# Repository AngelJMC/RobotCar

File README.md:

# RobotCar

It is a personal project to convert an old radio control car into a prototype autonomous vehicle. 
More information in the project [Wiki page](https://github.com/AngelJMC/RobotCar/wiki).

## Getting Started

- [AMP 2.6 board](https://github.com/ArduPilot/ardupilot_wiki/blob/master/common/source/docs/common-apm25-and-26-overview.rst). You can use Arduino Mega 2560.
- [L298 Driver](http://candy-ho.com/Drivers/Guia%20de%20Uso%20L298.pdf), It is a dual H-bridge to control de DC motor.
- [LM2596 regulator](https://http2.mlstatic.com/modulo-step-down-dc-dc-mini-regulador-de-voltaje-lm2596-D_NQ_NP_828400-MLC26118955337_102017-F.jpg) Step-down DC-DC converter module, ~12v LiPo battery to 5v.

Atom with [PlatformIO](https://platformio.org/) plugin. If you prefer, you can use Arduino IDE.

### Prerequisites

You need install the next arduino library:
- [Encoder@>=1.4.1](https://github.com/PaulStoffregen/Encoder)
- [L298N@>=1.1.0](https://github.com/AndreaLombardo/L298N)
- [PID@>=1.2.](https://github.com/br3ttb/Arduino-PID-Library)
  
All other required libraries are included in the repository.

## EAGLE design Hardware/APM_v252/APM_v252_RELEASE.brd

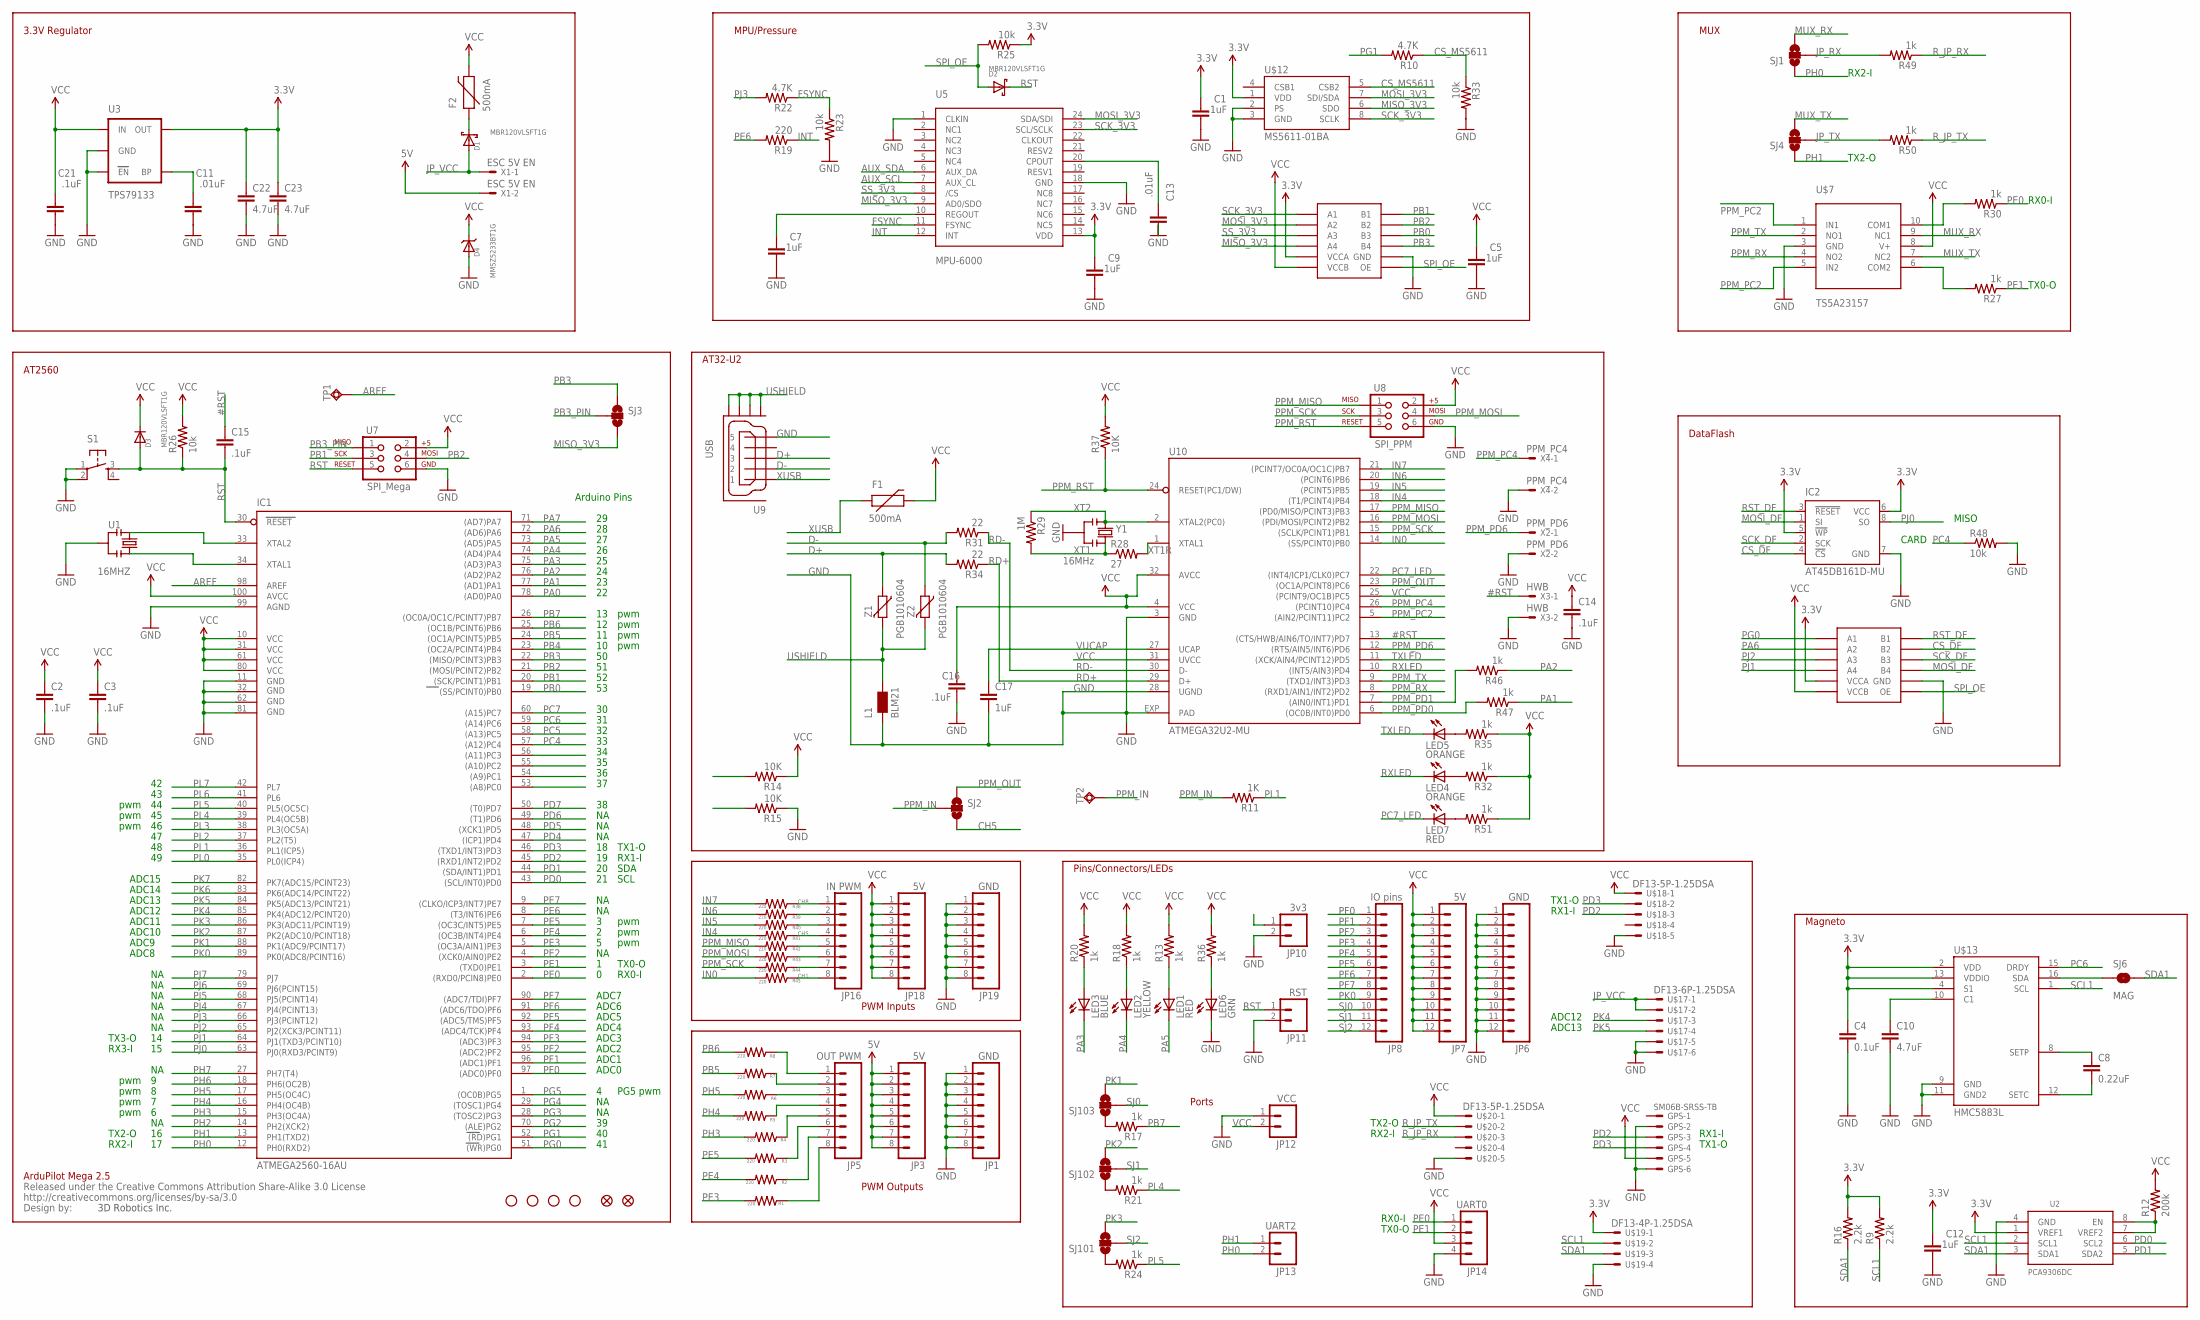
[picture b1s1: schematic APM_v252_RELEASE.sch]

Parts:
C1, C2, C3, C5, C7, C9, C12, C14, C15, C16, C21: .1uF; 0402-CAP
C4: 0.1uF; 0402-CAP
C8: 0.22uF; 0402-CAP
C10: 4.7uF; 1206
C11, C13: .01uF; 0402-CAP
C17: 1uF; 0402-CAP
C22, C23: 4.7uF; 0805
D1, D2, D3: MBR120VLSFT1G; SOD-123
D4: MMSZ5233BT1G; SOD-123
F1, F2: 500mA; PTC-1206
GPS: SM06B-SRSS-TB
IC1: ATMEGA2560-16AU; TQFP100
IC2: AT45DB161D-MU; VDFN-8-NO-BOTTOM-PAD
JP1, JP19: GND; 1X08
JP2, JP17: FIDUCIAL1X2; FIDUCIAL-1X2
JP3, JP18: 5V; 1X08
JP5: OUT PWM; 1X08
JP6: GND; 1X12
JP7: 5V; 1X12
JP8: IO pins; 1X12
JP10: 3v3; 1X02
JP11: RST; 1X02
JP12: VCC; 1X02
JP13: UART2; 1X02
JP14: UART0; 1X04
JP16: IN PWM; 1X08
L1: BLM21; 0805
LED1, LED7: RED; LED-0603
LED2: YELLOW; LED-0603
LED3: BLUE; LED-0603
LED4, LED5: ORANGE; LED-0603
LED6: GRN; LED-0603
R1, R2, R3, R4, R5, R6, R7, R8, R19, R38, R39, R40, R41, R42, R43, R44, R45: 220; 0402-RES
R9, R16: 2.2k; 0402-RES
R10, R22: 4.7K; 0402-RES
R11: 1K; 0402-RES
R12: 200k; 0402-RES
R13, R17, R18, R20, R21, R24, R27, R30, R32, R35, R36, R46, R47, R49, R50, R51: 1k; 0402-RES
R14, R15, R37: 10K; 0402-RES
R23, R25, R26, R33, R48: 10k; 0402-RES
R28: 27; 0402-RES
R29: 1M; 0402-RES
R31, R34: 22; 0402-RES
S1: TAC_SWITCHSMD; TACTILE_SWITCH_SMD
SJ1, SJ2, SJ3, SJ4: SOLDERJUMPER_2WAYT; SJ_2
SJ6: MAG; SJ_2S-TRACE
SJ101, SJ102, SJ103: SOLDERJUMPER_2WAYS; SJ_3
TP1, TP2: TPSQTP10SQ; TP10SQ
U1: 16MHZ; RESONATOR-SMD
U2: PCA9306DC; VSSOP8
U3: TPS79133; SOT23-5
U5: MPU-6000; QFN-24
U7: SPI_Mega; 2X3-NS
U8: SPI_PPM; 2X3-NS
U9: USB; MOLEX_MICRO_USB_AB_BOTTOM_MOUNT
U10: ATMEGA32U2-MU; QFN32
U$1, U$2, U$4, U$5: STAND-OFF
U$6: CREATIVE_COMMONS
U$7: TS5A23157; MSOP10
U$12: MS5611-01BA
U$13: HMC5883L; LPCC16
U$14, U$15: TXB0104UQFN; UQFN-12
U$17: DF13-6P-1.25DSA
U$18, U$20: DF13-5P-1.25DSA
U$19: DF13-4P-1.25DSA
X1: ESC 5V EN; 87758-0216
X2: PPM_PD6; 87758-0216
X3: HWB; 87758-0216
X4: PPM_PC4; 87758-0216
Y1: 16MHz; RESONATOR
Z1, Z2: PGB1010604; CT/CN0603

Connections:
3.3V: C1.2, C4.1, C9.2, C12.2, C22.1, C23.1, IC2.5 (!WP), IC2.6 (VCC), R9.2, R16.2, R25.1, U2.1 (VREF1), U3.5 (OUT), U5.13 (VDD), U$12.1 (VDD), U$13.2 (VDD), U$13.4 (S1), U$13.13 (VDDIO), U$14.1 (VCCA), U$15.1 (VCCA), U$19.1
5V: JP3.1, JP3.2, JP3.3, JP3.4, JP3.5, JP3.6, JP3.7, JP3.8, X1.2
#RST: C15.1, U10.13 ((CTS/HWB/AIN6/TO/INT7)PD7), X3.1
AREF: IC1.98 (AREF), TP1.TP
AUX_SCL: U5.7 (AUX_CL)
AUX_SDA: U5.6 (AUX_DA)
CH1: JP16.8, R45.1
CH5: JP16.4, R41.1, SJ2.3
CH8: JP16.1, R38.1
CS_DF: IC2.4 (!CS), U$15.9 (B2)
CS_MS5611: R10.1, R33.1, U$12.5 (CSB2)
D+: R34.2, U9.3, Z1.1
D-: R31.2, U9.2, Z2.1
FSYNC: R22.1, R23.1, U5.11 (FSYNC)
GND: C1.1, C2.2, C3.2, C4.2, C5.1, C7.1, C9.1, C10.2, C11.1, C12.1, C13.1, C14.2, C16.2, C17.2, C21.1, C22.2, C23.2, D4.A, GPS.2, GPS.6, IC1.11 (GND), IC1.32 (GND1), IC1.62 (GND2), IC1.81 (GND3), IC1.99 (AGND), IC2.7 (GND), JP1.1, JP1.2, JP1.3, JP1.4, JP1.5, JP1.6, JP1.7, JP1.8, JP6.1, JP6.2, JP6.3, JP6.4, JP6.5, JP6.6, JP6.7, JP6.8, JP6.9, JP6.10, JP6.11, JP6.12, JP10.2, JP11.2, JP12.1, JP14.4, JP19.1, JP19.2, JP19.3, JP19.4, JP19.5, JP19.6, JP19.7, JP19.8, L1.1, LED6.C, R15.1, R23.2, R33.2, R48.2, S1.1, S1.2, U1.2, U2.4 (GND), U3.2 (GND), U3.3 (EN), U5.1 (CLKIN), U5.18 (GND), U7.6, U8.6, U9.5, U10.3 (GND), U10.28 (UGND), U10.EXP (PAD), U$7.3 (GND), U$12.2 (PS), U$12.3 (GND), U$13.9 (GND), U$13.11 (GND2), U$14.6 (GND), U$15.6 (GND), U$17.5, U$17.6, U$18.5, U$19.4, U$20.5, X2.2, X3.2, X4.2, Y1.2
HI: IC1.54 ((A9)PC1), R14.2
IN0: R45.2, U10.14 ((SS/PCINT0)PB0)
IN4: R41.2, U10.18 ((T1/PCINT4)PB4)
IN5: R40.2, U10.19 ((PCINT5)PB5)
IN6: R39.2, U10.20 ((PCINT6)PB6)
IN7: R38.2, U10.21 ((PCINT7/OC0A/OC1C)PB7)
INT: R19.1, U5.12 (INT)
JP_RX: R49.2, SJ1.2
JP_TX: R50.2, SJ4.2
JP_VCC: D1.A, U$17.1, U$17.2, X1.1
LO: IC1.53 ((A8)PC0), IC1.55 ((A10)PC2), IC1.56 ((A11)PC3), R15.2
MISO_3V3: SJ3.3, U5.9 (AD0/SDO), U$12.6 (SDO), U$14.5 (A4)
MOSI_3V3: U5.24 (SDA/SDI), U$12.7 (SDI/SDA), U$14.3 (A2)
MOSI_DF: IC2.1 (SI), U$15.7 (B4)
MUX_RX: SJ1.3, U$7.9 (NC1)
MUX_TX: SJ4.3, U$7.7 (NC2)
unnamed: LED6.A, R36.1
unnamed: C13.2, U5.20 (CPOUT)
unnamed: C7.2, U5.10 (REGOUT)
unnamed: D1.C, F2.1
unnamed: C11.2, U3.4 (BP)
unnamed: C10.1, U$13.10 (C1)
unnamed: JP5.5, R4.1
unnamed: JP5.6, R3.1
unnamed: JP5.7, R2.1
unnamed: JP5.8, R1.1
unnamed: R12.1, U2.7 (VREF2), U2.8 (EN)
unnamed: JP5.4, R5.1
unnamed: JP5.3, R6.1
unnamed: JP5.2, R7.1
unnamed: JP5.1, R8.1
unnamed: LED7.A, R51.2
unnamed: JP16.2, R39.1
unnamed: JP16.3, R40.1
unnamed: JP16.5, R42.1
unnamed: JP16.6, R43.1
unnamed: JP16.7, R44.1
unnamed: SJ6.1, U$13.16 (SDA)
unnamed: C8.1, U$13.8 (SETP)
unnamed: C8.2, U$13.12 (SETC)
unnamed: LED1.A, R13.1
unnamed: LED5.A, R35.2
unnamed: LED4.A, R32.2
unnamed: LED2.A, R18.1
unnamed: R30.2, U$7.10 (COM1)
unnamed: R27.2, U$7.6 (COM2)
unnamed: LED3.A, R20.1
unnamed: R17.2, SJ103.1
unnamed: R24.2, SJ101.1
unnamed: R21.2, SJ102.1
unnamed: IC1.34 (XTAL1), U1.3
unnamed: IC1.33 (XTAL2), U1.1
PA0: IC1.78 ((AD0)PA0)
PA1: IC1.77 ((AD1)PA1), R47.1
PA2: IC1.76 ((AD2)PA2), R46.1
PA3: IC1.75 ((AD3)PA3), LED3.C
PA4: IC1.74 ((AD4)PA4), LED2.C
PA5: IC1.73 ((AD5)PA5), LED1.C
PA6: IC1.72 ((AD6)PA6), U$15.3 (A2)
PA7: IC1.71 ((AD7)PA7)
PB0: IC1.19 ((SS/PCINT0)PB0), U$14.8 (B3)
PB1: IC1.20 ((SCK/PCINT1)PB1), U7.3, U$14.10 (B1)
PB2: IC1.21 ((MOSI/PCINT2)PB2), U7.4, U$14.9 (B2)
PB3: IC1.22 ((MISO/PCINT3)PB3), SJ3.1, U$14.7 (B4)
PB3_PIN: SJ3.2, U7.1
PB4: IC1.23 ((OC2A/PCINT4)PB4)
PB5: IC1.24 ((OC1A/PCINT5)PB5), R7.2
PB6: IC1.25 ((OC1B/PCINT6)PB6), R8.2
PB7: IC1.26 ((OC0A/OC1C/PCINT7)PB7), R17.1
PC4: IC1.57 ((A12)PC4), R48.1
PC5: IC1.58 ((A13)PC5)
PC6: IC1.59 ((A14)PC6), U$13.15 (DRDY)
PC7: IC1.60 ((A15)PC7)
PC7_LED: LED7.C, U10.22 ((INT4/ICP1/CLK0)PC7)
PD0: IC1.43 ((SCL/INT0)PD0), U2.6 (SCL2)
PD1: IC1.44 ((SDA/INT1)PD1), U2.5 (SDA2)
PD2: GPS.3, IC1.45 ((RXD1/INT2)PD2), U$18.3
PD3: GPS.4, IC1.46 ((TXD1/INT3)PD3), U$18.2
PD4: IC1.47 ((ICP1)PD4)
PD5: IC1.48 ((XCK1)PD5)
PD6: IC1.49 ((T1)PD6)
PD7: IC1.50 ((T0)PD7)
PE0: IC1.2 ((RXD0/PCIN8)PE0), JP14.1, R30.1
PE1: IC1.3 ((TXD0)PE1), JP14.2, R27.1
PE2: IC1.4 ((XCK0/AIN0)PE2)
PE3: IC1.5 ((OC3A/AIN1)PE3), R1.2
PE4: IC1.6 ((OC3B/INT4)PE4), R2.2
PE5: IC1.7 ((OC3C/INT5)PE5), R3.2
PE6: IC1.8 ((T3/INT6)PE6), R19.2
PE7: IC1.9 ((CLKO/ICP3/INT7)PE7)
PF0: IC1.97 ((ADC0)PF0), JP8.1
PF1: IC1.96 ((ADC1)PF1), JP8.2
PF2: IC1.95 ((ADC2)PF2), JP8.3
PF3: IC1.94 ((ADC3)PF3), JP8.4
PF4: IC1.93 ((ADC4/TCK)PF4), JP8.5
PF5: IC1.92 ((ADC5/TMS)PF5), JP8.6
PF6: IC1.91 ((ADC6/TDO)PF6), JP8.7
PF7: IC1.90 ((ADC7/TDI)PF7), JP8.8
PG0: IC1.51 ((WR)PG0), U$15.2 (A1)
PG1: IC1.52 ((RD)PG1), R10.2
PG2: IC1.70 ((ALE)PG2)
PG3: IC1.28 ((TOSC2)PG3)
PG4: IC1.29 ((TOSC1)PG4)
PG5: IC1.1 ((OC0B)PG5)
PH0: IC1.12 (PH0(RXD2)), JP13.2, SJ1.1
PH1: IC1.13 (PH1(TXD2)), JP13.1, SJ4.1
PH2: IC1.14 (PH2(XCK2))
PH3: IC1.15 (PH3(OC4A)), R4.2
PH4: IC1.16 (PH4(OC4B)), R5.2
PH5: IC1.17 (PH5(OC4C)), R6.2
PH6: IC1.18 (PH6(OC2B))
PH7: IC1.27 (PH7(T4))
PJ0: IC1.63 (PJ0(RXD3/PCINT9)), IC2.8 (SO)
PJ1: IC1.64 (PJ1(TXD3/PCINT10)), U$15.5 (A4)
PJ2: IC1.65 (PJ2(XCK3/PCINT11)), U$15.4 (A3)
PJ3: IC1.66 (PJ3(PCINT12)), R22.2
PJ4: IC1.67 (PJ4(PCINT13))
PJ5: IC1.68 (PJ5(PCINT14))
PJ6: IC1.69 (PJ6(PCINT15))
PJ7: IC1.79 (PJ7)
PK0: IC1.89 (PK0(ADC8/PCINT16)), JP8.9
PK1: IC1.88 (PK1(ADC9/PCINT17)), SJ103.3
PK2: IC1.87 (PK2(ADC10/PCINT18)), SJ102.3
PK3: IC1.86 (PK3(ADC11/PCINT19)), SJ101.3
PK4: IC1.85 (PK4(ADC12/PCINT20)), U$17.3
PK5: IC1.84 (PK5(ADC13/PCINT21)), U$17.4
PK6: IC1.83 (PK6(ADC14/PCINT22))
PK7: IC1.82 (PK7(ADC15/PCINT23))
PL0: IC1.35 (PL0(ICP4))
PL1: IC1.36 (PL1(ICP5)), R11.1
PL2: IC1.37 (PL2(T5))
PL3: IC1.38 (PL3(OC5A))
PL4: IC1.39 (PL4(OC5B)), R21.1
PL5: IC1.40 (PL5(OC5C)), R24.1
PL6: IC1.41 (PL6)
PL7: IC1.42 (PL7)
PPM_IN: R11.2, SJ2.2, TP2.TP
PPM_MISO: R42.2, U8.1, U10.17 ((PD0/MISO/PCINT3)PB3)
PPM_MOSI: R43.2, U8.4, U10.16 ((PDI/MOSI/PCINT2)PB2)
PPM_OUT: SJ2.1, U10.23 ((OC1A/PCINT8)PC6)
PPM_PC2: U10.5 ((AIN2/PCINT11)PC2), U$7.1 (IN1), U$7.5 (IN2)
PPM_PC4: U10.26 ((PCINT10)PC4), X4.1
PPM_PD0: R47.2, U10.6 ((OC0B/INT0)PD0)
PPM_PD1: R46.2, U10.7 ((AIN0/INT1)PD1)
PPM_PD6: U10.12 ((RTS/AIN5/INT6)PD6), X2.1
PPM_RST: R37.1, U8.5, U10.24 (RESET(PC1/DW))
PPM_RX: U10.8 ((RXD1/AIN1/INT2)PD2), U$7.4 (NO2)
PPM_SCK: R44.2, U8.3, U10.15 ((SCLK/PCINT1)PB1)
PPM_TX: U10.9 ((TXD1/INT3)PD3), U$7.2 (NO1)
RD+: R34.1, U10.29 (D+)
RD-: R31.1, U10.30 (D-)
RST: C15.2, D2.C, D3.A, IC1.30 (RESET), JP11.1, R26.1, S1.3, U7.5
RST_DF: IC2.3 (!RESET), U$15.10 (B1)
RXLED: LED4.C, U10.10 ((INT5/AIN3)PD4)
R_JP_RX: R49.1, U$20.3
R_JP_TX: R50.1, U$20.2
SCK_3V3: U5.23 (SCL/SCLK), U$12.8 (SCLK), U$14.2 (A1)
SCK_DF: IC2.2 (SCK), U$15.8 (B3)
SCL1: R9.1, U2.2 (SCL1), U$13.1 (SCL), U$19.2
SDA1: R16.1, SJ6.2, U2.3 (SDA1), U$19.3
SJ0: JP8.10, SJ103.2
SJ1: JP8.11, SJ102.2
SJ2: JP8.12, SJ101.2
SPI_OE: D2.A, R25.2, U$14.12 (OE), U$15.12 (OE)
SS_3V3: U5.8 (/CS), U$14.4 (A3)
TXLED: LED5.C, U10.11 ((XCK/AIN4/PCINT12)PD5)
USHIELD: L1.2, U9.GND1, U9.GND2, U9.GND3, U9.GND4, Z1.2, Z2.2
VCC: C2.1, C3.1, C5.2, C14.1, C16.1, C21.2, D3.C, D4.C, F1.2, F2.2, GPS.5, IC1.10 (VCC), IC1.31 (VCC1), IC1.61 (VCC2), IC1.80 (VCC3), IC1.100 (AVCC), JP7.1, JP7.2, JP7.3, JP7.4, JP7.5, JP7.6, JP7.7, JP7.8, JP7.9, JP7.10, JP7.11, JP7.12, JP12.2, JP14.3, JP18.1, JP18.2, JP18.3, JP18.4, JP18.5, JP18.6, JP18.7, JP18.8, R12.2, R13.2, R14.1, R18.2, R20.2, R26.2, R32.1, R35.1, R36.2, R37.2, R51.1, U3.1 (IN), U7.2, U8.2, U10.4 (VCC), U10.25 ((PCINT9/OC1B)PC5), U10.31 (UVCC), U10.32 (AVCC), U$7.8 (V+), U$14.11 (VCCB), U$15.11 (VCCB), U$18.1, U$20.1
VUCAP: C17.1, U10.27 (UCAP)
XT1: R28.1, R29.2, Y1.3
XT1R: R28.2, U10.1 (XTAL1)
XT2: R29.1, U10.2 (XTAL2(PC0)), Y1.1
XUSB: F1.1, U9.1

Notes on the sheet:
ADC0
ADC1
ADC2
ADC3
ADC4
ADC5
ADC6
ADC7
ADC8
ADC9
ADC10
ADC11
ADC12
ADC13
ADC14
ADC15
RX1-I
TX1-O
TX0-O
RX0-I
RX2-I
TX2-O
TX3-O
RX3-I
SDA
SCL
pwm
PG5 pwm
PWM Outputs
PWM Inputs
Ports
ArduPilot Mega 2.5
Arduino Pins
3D Robotics Inc.
CARD
MISO
DataFlash
MUX
MPU/Pressure
AT32-U2

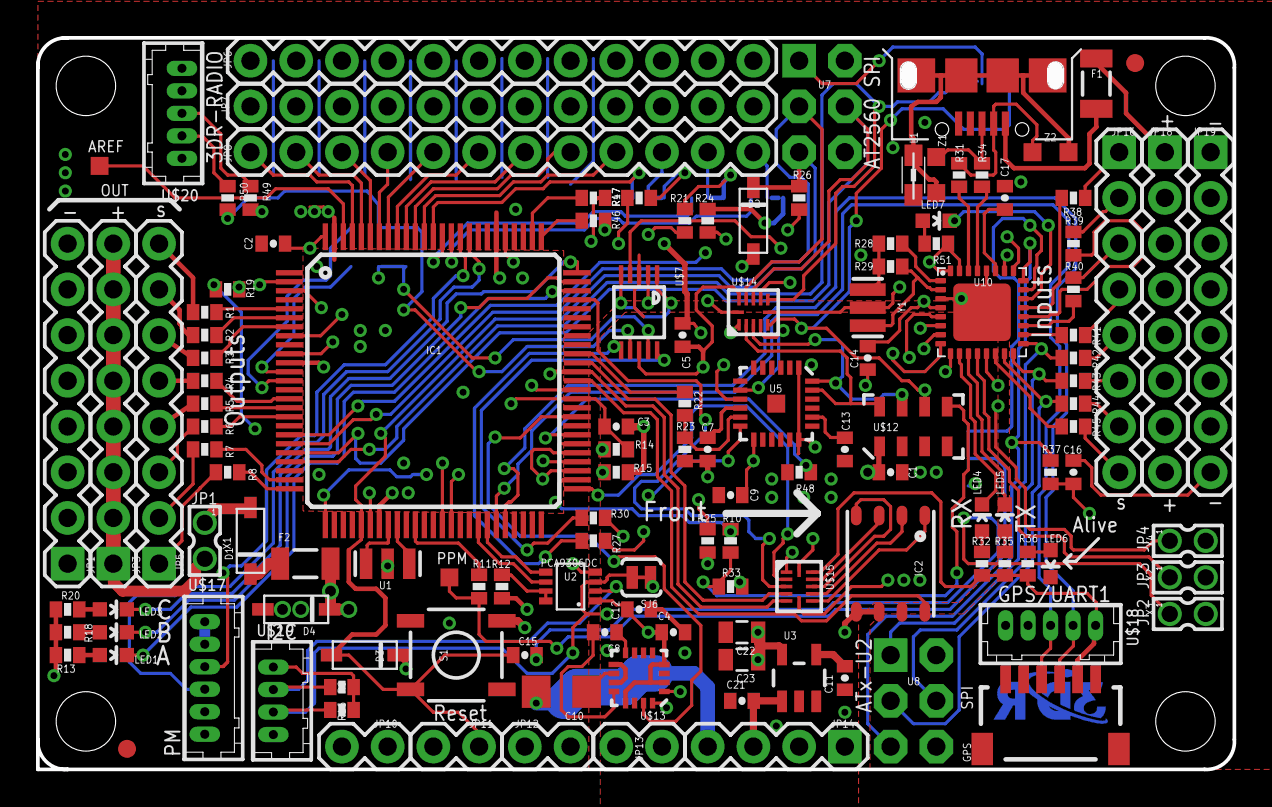
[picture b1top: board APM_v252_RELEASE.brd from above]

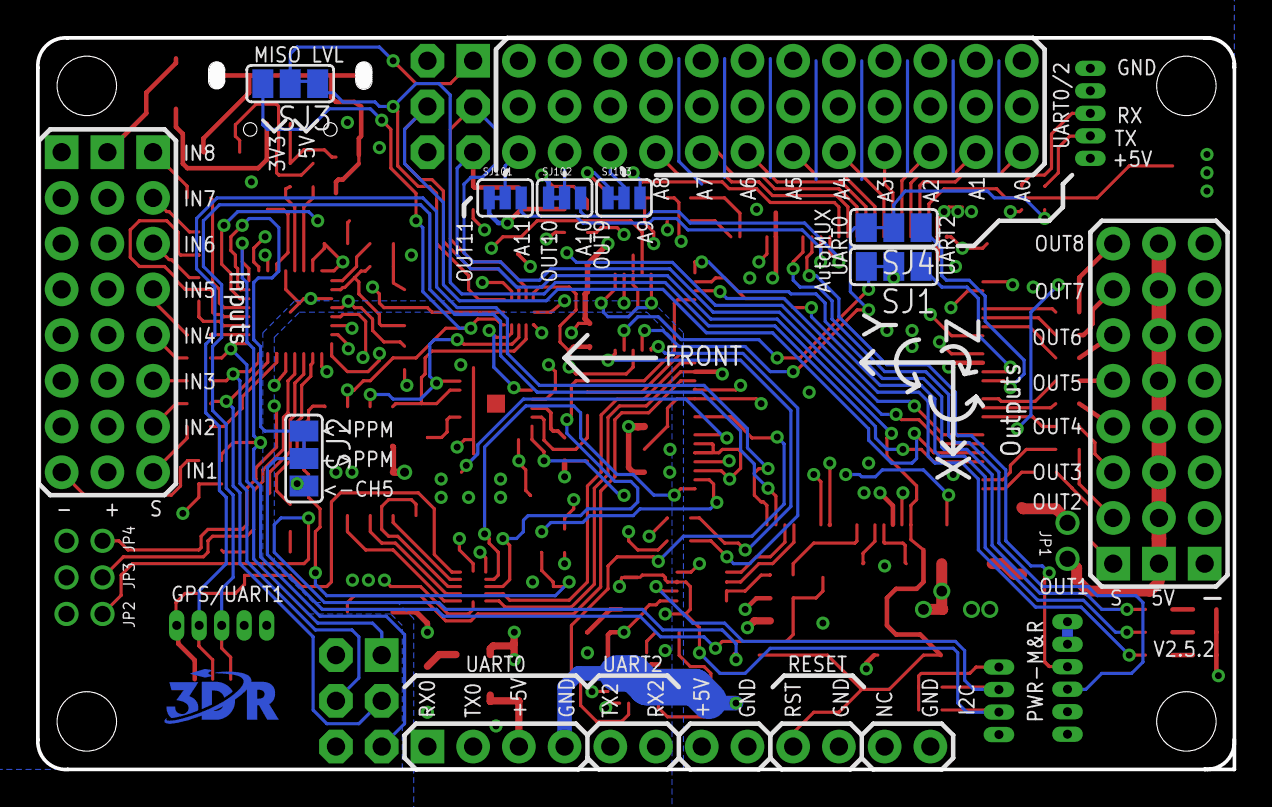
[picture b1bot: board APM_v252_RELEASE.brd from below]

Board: 4 copper layers, 66.5 x 40.6 mm, 144 parts (8 on the bottom side), 157 nets.

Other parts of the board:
U$21: 3DR-LOGO-025IN-METAL

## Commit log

2017-06-10 Added APM2.6 Eagle Files Created Arduino project with firmware to control motor and servo. Defined port to control L298N
2017-06-10 Added PID library by Brett Beauregard <br3ttb@gmail.com> brettbeauregard.com
2017-06-14 Changed IDE for Arduino. Now I set Sloeber, a IDE based on Eclipse http://www.baeyens.it/eclipse/
2017-10-21 Changed IDE in use. New configuration for PlatformIO
2017-11-04 Added 3D model for encoder and sensor support
2017-11-04 Moved 3D servo support
2018-01-28 Added motorControl library. Motor driver (l298N) and encoder library are instantiated here.
2018-02-15 Added Arduino Servo library by Michael Margolis. version = 1.1.2
2018-02-15 Added Radio Control Library for Ardupilot Mega 2.0. Arduino Code by Jordi Muñoz and Jose Julio. DIYDrones.com. This library has been simplified to use only PPM Decoder option, removed pwm output func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
2018-02-15 Added Arduino Mega ISR Registry, it has been modified to set only TIMER5_CAPT_vect ISR
2018-02-15 timer16_Sequence_t enumerates has been modified to avoid problem with TIMER_5_CAPTURE
2018-02-15 Implemented in main function the RC control features.
2018-02-15 Added new images for wiki documentation
2018-02-19 New image for doc
2018-02-26 Implemented PID for speed control of the motor.
2018-02-28 Important code refactoring and library creation: cli, control and rc_command. No new features have been added.
2018-03-05 Added new AP libraries
2018-03-05 Remplaced prog_char to char, prog_char was deprecated
2018-04-14 New IR sensors holder. Work in progress...
2018-04-14 Added libraries to inertial sensor
2018-04-15 Added new 3D part to hold the IR distance sensors
2018-06-12 Refactor of motorControl library
    Now it is implemented like a c++ class
2018-06-16 Added Infra-red library sensors
    Added new library to read the infra-red sensors array
2018-06-16 Changed name of motor control library
2018-06-16 Added irSensors read to main loop
2018-06-16 Removed dead code
2018-06-17 Removed old library: control.h and control.cpp Added servo control from rc_command
2018-06-22 Testing rosserial communication
2018-08-01 Added Octave script with the steering angle test
2018-08-01 Refactor motor control library
2018-09-11 Improved main.cpp file

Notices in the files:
parts and their libraries:
SparkFun: Released under the Creative Commons Attribution Share-Alike 3.0 License
SparkFun: http://creativecommons.org/licenses/by-sa/3.0
